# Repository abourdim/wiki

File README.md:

# Wiki

Personal notes and how-to guides.

Every article is available in French (default), English, and Arabic (RTL). The bare filename is the French version; add `-en` or `-ar` for the other languages (e.g. `bit-rxy.html` = French, `bit-rxy-en.html` = English, `bit-rxy-ar.html` = Arabic). Each page has a language switcher in its masthead.

## Contents

- Sharing Files Between Ubuntu & Windows 11 — Step-by-step guide to setting up SMB file sharing in both directions on a local network, plus RDP and troubleshooting notes. [FR](windows-ubuntu-file-sharing-tutorial.html) · [EN](windows-ubuntu-file-sharing-tutorial-en.html) · [AR](windows-ubuntu-file-sharing-tutorial-ar.html)
- VideoCar — Enhanced firmware and web control page for the keyestudio ESP32-CAM Video Smart Car: joystick control, failsafe, live Vision overlays, autonomous Follow-me/Line/Colour-chase modes. [FR](video-car.html) · [EN](video-car-en.html) · [AR](video-car-ar.html)
- Bit-Bot — AI robot companion for kids: voice chat with a choice of AI providers, 12 personalities, AI-powered mini-games, and an optional BBC micro:bit link over Bluetooth. [FR](bit-bot.html) · [EN](bit-bot-en.html) · [AR](bit-bot-ar.html)
- Talking Robot — Browser speech & emotion robot: text-to-speech, speech recognition, 13 animated emotions, and an optional BBC micro:bit link over Bluetooth. No AI provider, fully offline. [FR](talking-robot.html) · [EN](talking-robot-en.html) · [AR](talking-robot-ar.html)
- micro:bit Playground — 8-tab BLE control panel and sensor dashboard for the BBC micro:bit V2: live sensor graphing, servo control, 5 interactive 3D robot models, and a 30+ command firmware protocol. [FR](bit-playground.html) · [EN](bit-playground-en.html) · [AR](bit-playground-ar.html)
- Micro:bit Remote Builder (bit-rxy) — Drag-and-drop BLE remote-control builder: design a layout from 12 widget types and it generates matching MakeCode firmware automatically, with one-click flashing over Bluetooth Partial Flashing Service or WebUSB. [FR](bit-rxy.html) · [EN](bit-rxy-en.html) · [AR](bit-rxy-ar.html)
- ESP32-RXY — ESP32 firmware that impersonates a BBC micro:bit's BLE UART protocol, so the unmodified rxy web app can connect to a plain ESP32-C3 and drive widgets exactly as it would a real micro:bit. [FR](esp32-rxy.html) · [EN](esp32-rxy-en.html) · [AR](esp32-rxy-ar.html)
- rxy-web — The universal Bluetooth remote for rxy robots: the robot owns the layout, so the app knows no robot in advance — it asks whichever one it just found to send its own interface, then draws it. 20 widget types, a layout-fingerprint cache, and a radar fed by two values the robot already sends. [FR](rxy-web.html) · [EN](rxy-web-en.html) · [AR](rxy-web-ar.html)
- Servo-Sonar — A reduced bit-rxy: two continuous-rotation drive servos, one HC-SR04, and nothing else. Four firmware-served panels, and per-wheel trim sliders that are set from the app while driving and kept in NVS. [FR](servo-sonar.html) · [EN](servo-sonar-en.html) · [AR](servo-sonar-ar.html)
- ESP32-CAM Robot -- Wi-Fi rover on a single ESP32-CAM: live MJPEG video, two motors on a TB6612FNG, record-and-replay programs kept on the robot, and a web interface the firmware serves itself. Includes the LEDC timer collision that let the camera clock silently saturate the left motor's PWM. [FR](cam-robot.html) · [EN](cam-robot-en.html) · [AR](cam-robot-ar.html)
- ESP32-CAM Robot m1 -- The same ESP32-CAM with a different motor board: one low-side MOSFET per motor, so no reverse at all. What it has instead is colour following computed in the browser, an engine sound whose pitch tracks the motor PWM, and a captive portal that opens the robot page without anyone typing an address. [FR](cam-robot-m1.html) · [EN](cam-robot-m1-en.html) · [AR](cam-robot-m1-ar.html)
- ESP32-CAM plugin board — ESPHome validation -- An ESPHome test firmware that checks every part of a freshly assembled ESP32-CAM plugin board from a web page: OLED, RGB LED, two L9110 motors, camera and power supply. Pinout taken from the schematic, live camera settings, and the ESPHome traps met during bring-up. Configuration: [files/esp32_cam_test.yaml](files/esp32_cam_test.yaml). KiCad project: [files/esp32_cam_plugin/](files/esp32_cam_plugin/). [FR](cam-plugin-esphome.html) · [EN](cam-plugin-esphome-en.html) · [AR](cam-plugin-esphome-ar.html)
- ESP32-CAM Robot v2 — ESPHome firmware -- Robot firmware for the ESP32-CAM + plugin board v3 (L9110s not fitted) + robot board v2 stack: TB6612 differential drive from a web page or REST, speed ramp, brake, command timeout and stop on link loss, four status RGB LEDs, OLED pages and MJPEG video. Ships with launch.sh, a coloured menu for kids that shows every command it runs. Configuration: [files/esp32_cam_robot.yaml](files/esp32_cam_robot.yaml). Helper: [files/launch.sh](files/launch.sh). KiCad and production files: [files/esp32_cam_robot_v2/](files/esp32_cam_robot_v2/) and [files/esp32_cam_plugin_v3/](files/esp32_cam_plugin_v3/). [FR](cam-robot-esphome.html) · [EN](cam-robot-esphome-en.html) · [AR](cam-robot-esphome-ar.html)

## Index

Open [index.html](index.html) (French), [index-en.html](index-en.html), or [index-ar.html](index-ar.html) for a browsable landing page of all guides.

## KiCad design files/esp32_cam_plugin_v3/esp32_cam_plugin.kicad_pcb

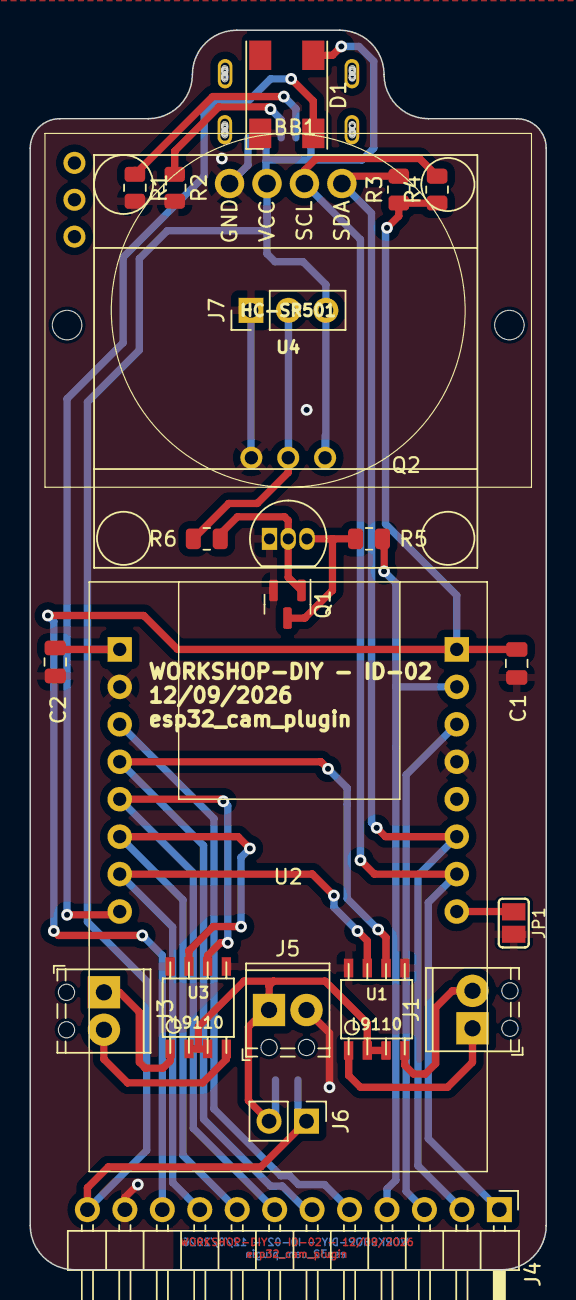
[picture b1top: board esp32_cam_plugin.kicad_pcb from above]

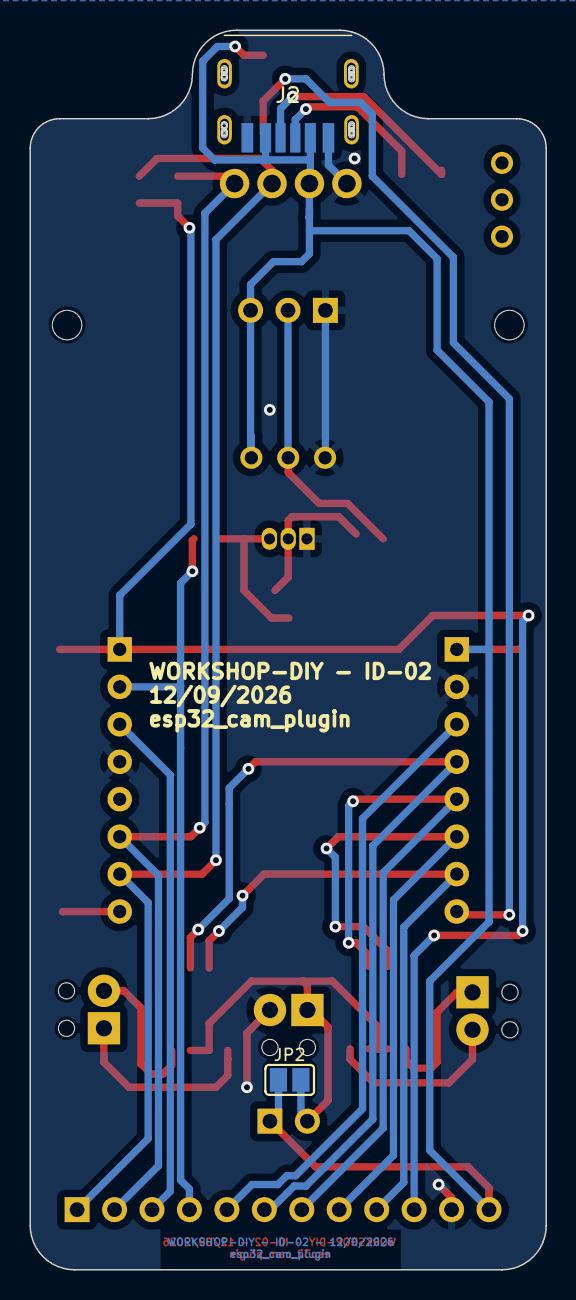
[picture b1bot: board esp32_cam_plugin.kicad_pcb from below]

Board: 2 copper layers, 35.0 x 84.1 mm, 25 parts (2 on the bottom side), 24 nets.

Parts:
BB1: oled_128x32; oled_128X64_no_holes
C1, C2: 100nF; C_0805_2012Metric
D1: led_tx1812db_5050; led_tx1812cxa_5050_hand_soldering
J1, J3, J5: Screw_Terminal_01x02; TerminalBlock_Phoenix_MPT-0,5-2-2.54_1x02_P2.54mm_Horizontal
J2: USB_C_Receptacle_PowerOnly_6P; TYPEC31M17
J4: Conn_01x12_Pin; PinHeader_1x12_P2.54mm_Horizontal
J6: Conn_01x02_Pin; PinHeader_1x02_P2.54mm_Vertical
J7: Conn_01x03_Pin; PinHeader_1x03_P2.54mm_Vertical
JP1, JP2: SolderJumper_2_Open; SJ_OPEN
Q1: MMBT3904; SOT-23
Q2: 2N3904; TO-92_Inline
R1, R2: 5.1K; R_0805_2012Metric
R3, R4: 10K; R_0805_2012Metric
R5: 10k; R_0805_2012Metric
R6: 1k; R_0805_2012Metric
U1, U3: L9110; so-8
U2: ESP32-CAM
U4: HC-SR501

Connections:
3V3: C1.1, J4.10, R3.1, R4.1, U2.9 (3V3)
+5V: BB1.2 (VCC), C2.1, D1.1 (VDD), J2.A9 (VBUS), J2.B9 (VBUS), J4.12, J6.1, J7.3, JP2.1 (A), U2.8 (5V), U4.6 (VCC)
GND: BB1.1 (GND), C1.2, C2.2, D1.3 (GND), J2.A12 (GND), J2.B12 (GND), J4.11, J5.2, J7.1, JP1.2 (B), Q1.2 (E), Q2.1 (E), R1.2, R2.2, U1.5 (GND), U1.8 (GND), U2.7 (GND_1), U2.12 (GND_2), U3.5 (GND), U3.8 (GND), U4.4 (GND)
unnamed: J1.1, U1.1 (OA)
unnamed: J1.2, U1.4 (OB)
unnamed: J2.A5 (CC1), R2.1
unnamed: J2.B5 (CC2), R1.1
unnamed: J3.1, U3.1 (OA)
unnamed: J3.2, U3.4 (OB)
unnamed: J7.2, R6.1, U4.5 (VOUT)
unnamed: JP1.1 (A), U2.16 (GND_3)
unnamed: Q1.1 (B), Q2.2 (B), R6.2
unnamed: Q1.3 (C), Q2.3 (C), R5.1
VCC: J5.1, J6.2, JP2.2 (B), U1.2 (VCC), U1.3 (VCC), U3.2 (VCC), U3.3 (VCC)
esp32_io_00: J4.3, U2.11 (IO0)
esp32_io_02: J4.9, U1.7 (IB), U2.2 (IO2)
esp32_io_04: D1.4 (DIN), U2.1 (IO4)
esp32_io_12: J4.5, U2.6 (IO12)
esp32_io_13: J4.6, U1.6 (IA), U2.5 (IO13)
esp32_io_14: J4.8, U2.3 (IO14), U3.7 (IB)
esp32_io_15: J4.7, U2.4 (IO15), U3.6 (IA)
esp32_io_16: J4.4, R5.2, U2.10 (IO16)
ftdi_rx: BB1.3 (SCL), J4.1, R4.2, U2.15 (U0T)
ftdi_tx: BB1.4 (SDA), J4.2, R3.2, U2.14 (U0R)

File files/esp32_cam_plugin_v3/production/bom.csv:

Designator,Footprint,Quantity,Value,LCSC Part #
BB1,oled_128X64_no_holes,1,oled_128x32,
"C1, C2",0805,2,100nF,
D1,led_tx1812cxa_5050_hand_soldering,1,led_tx1812db_5050,
"J1, J3, J5","TerminalBlock_Phoenix_MPT-0,5-2-2.54_1x02_P2.54mm_Horizontal",3,Screw_Terminal_01x02,
J2,TYPEC31M17,1,USB_C_Receptacle_PowerOnly_6P,
J4,PinHeader_1x12_P2.54mm_Horizontal,1,Conn_01x12_Pin,
J6,PinHeader_1x02_P2.54mm_Vertical,1,Conn_01x02_Pin,
J7,PinHeader_1x03_P2.54mm_Vertical,1,Conn_01x03_Pin,
"JP1, JP2",SJ_OPEN,2,SolderJumper_2_Open,
Q1,SOT-23,1,MMBT3904,
Q2,TO-92_Inline,1,2N3904,
"R1, R2",0805,2,5.1K,
"R3, R4, R5",0805,3,10K,
R6,0805,1,1k,
"U1, U3",so-8,2,L9110,
U2,ESP32-CAM,1,ESP32-CAM,
U4,HC-SR501,1,HC-SR501,

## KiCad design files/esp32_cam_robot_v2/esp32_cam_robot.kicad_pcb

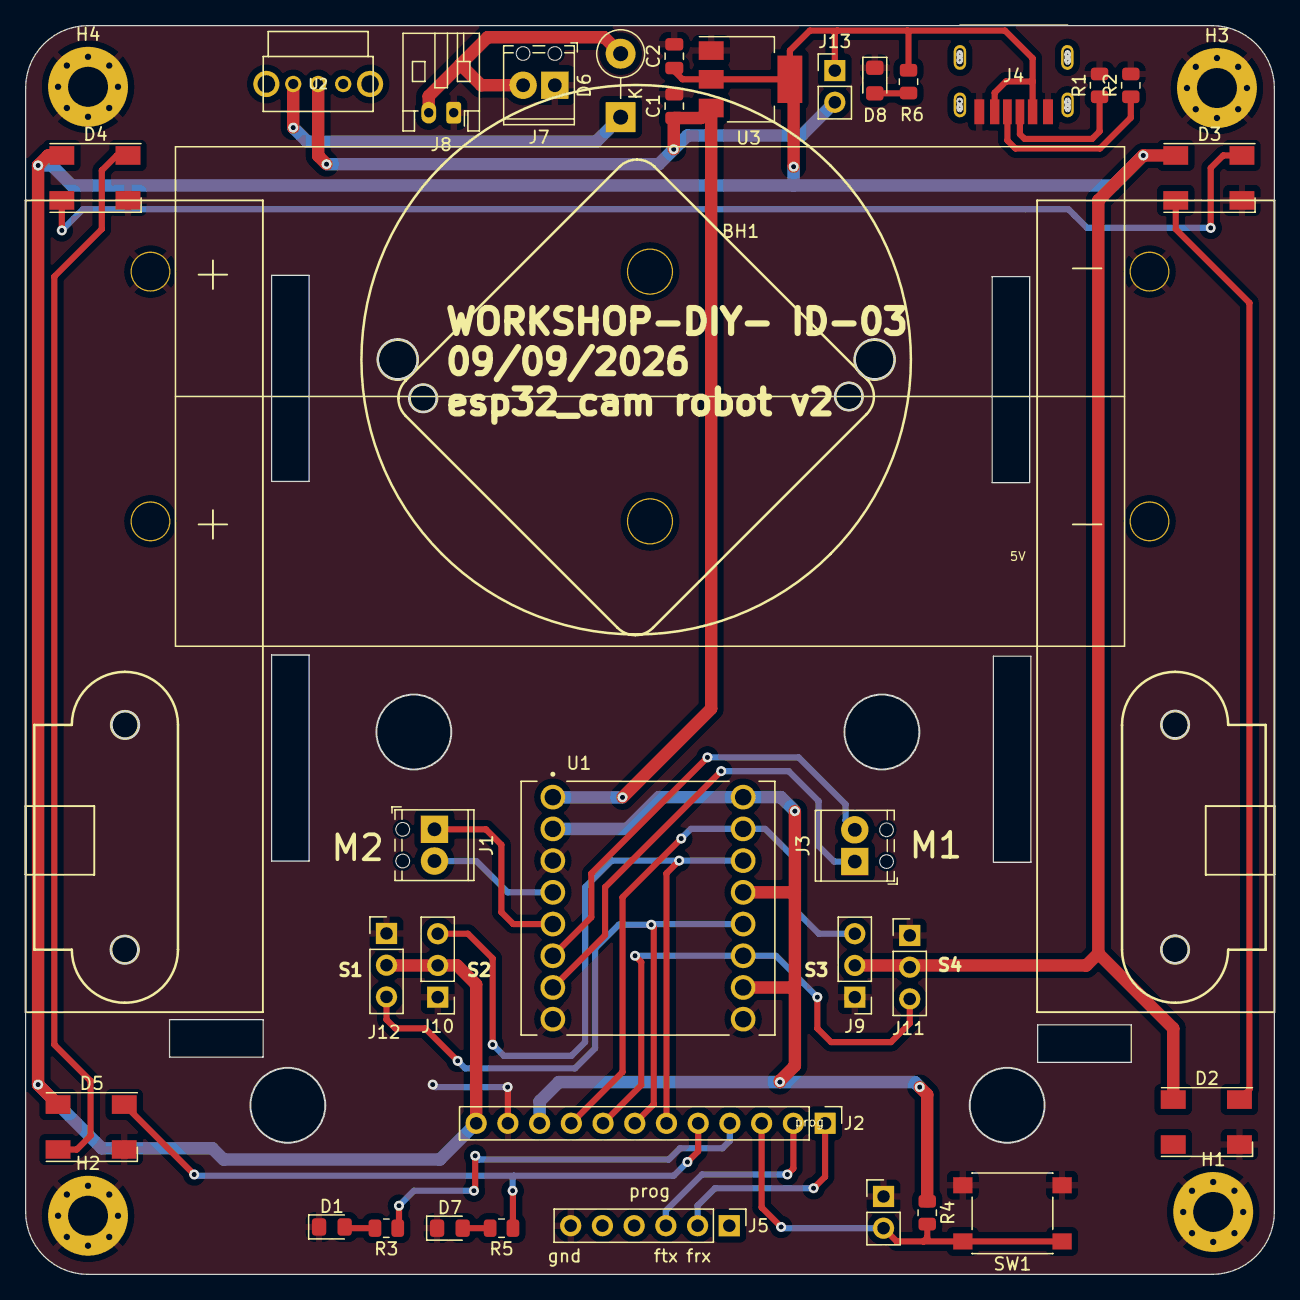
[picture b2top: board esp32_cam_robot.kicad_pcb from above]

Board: 2 copper layers, 100.0 x 100.0 mm, 38 parts (0 on the bottom side), 27 nets.

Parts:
BH1: HOLDER_18650; holder_18650_2
C1, C2: C; C_0805_2012Metric
D1, D7, D8: LED; LED_0805_2012Metric_Pad1.15x1.40mm_HandSolder
D2, D3, D4, D5: led_tx1812db_3528; led_tx1812cxa_5050_hand_soldering
D6: 1N4007; D_DO-15_P5.08mm_Vertical_KathodeUp
H1, H2, H3, H4: MountingHole_Pad; MountingHole_3.2mm_M3_Pad_Via
J1, J3, J7: Screw_Terminal_01x02; TerminalBlock_Phoenix_MPT-0,5-2-2.54_1x02_P2.54mm_Horizontal
J2: Conn_01x12_Pin; PinHeader_1x12_P2.54mm_Vertical
J4: USB_C_Receptacle_PowerOnly_6P; TYPEC31M17
J5: Conn_01x06_Pin; PinHeader_1x06_P2.54mm_Vertical
J6, J13: Conn_01x02_Pin; PinHeader_1x02_P2.54mm_Vertical
J8: Conn_01x02_Pin; JST_PH_S2B-PH-K_1x02_P2.00mm_Horizontal
J9, J10, J11, J12: Conn_01x03_Pin; PinHeader_1x03_P2.54mm_Vertical
R1, R2: 5.1K; R_0805_2012Metric
R3, R5, R6: R; R_0805_2012Metric
R4: 10k; R_0805_2012Metric
SW1: SW_Omron_B3FS; SW_Push_1P1T_NO_6x6mm_H9.5mm
U1: ROB-14450; MODULE_ROB-14450
U2: SK12D07VG4
U3: AMS1117-5.0; SOT-223-3_TabPin2

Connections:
3V3: J2.10, R4.1, U1.2 (VCC), U1.10 (PWMB), U1.13 (STBY), U1.16 (PWMA)
+5V: C2.1, D2.1 (VDD), D3.1 (VDD), D4.1 (VDD), D5.1 (VDD), J2.12, J4.A9 (VBUS), J4.B9 (VBUS), J9.2, J10.2, J11.2, J12.2, J13.1, R6.1, U3.2 (VO)
GND: BH1.1 (+), BH1.2 (-), C1.2, C2.2, D1.1 (K), D2.3 (GND), D3.3 (GND), D4.3 (GND), D5.3 (GND), D7.1 (K), D8.1 (K), H1.1, H2.1, H3.1, H4.1, J2.11, J4.A12 (GND), J4.B12 (GND), J5.6, J6.1, J7.1, J8.1, J9.1, J10.1, J11.1, J12.1, R1.2, R2.2, SW1.2, U1.3 (GND), U1.8 (GND), U1.9 (GND), U3.1 (GND)
unnamed: D1.2 (A), R3.2
unnamed: D2.4 (DIN), D3.2 (DOUT)
unnamed: D3.4 (DIN), D4.2 (DOUT)
unnamed: D4.4 (DIN), D5.2 (DOUT)
unnamed: D6.1 (K), U2.2
unnamed: D7.2 (A), R5.2
unnamed: D8.2 (A), R6.2
unnamed: J1.1, U1.5 (A02)
unnamed: J1.2, U1.4 (A01)
unnamed: J3.1, U1.7 (B01)
unnamed: J3.2, U1.6 (B02)
unnamed: J4.A5 (CC1), R1.1
unnamed: J4.B5 (CC2), R2.1
VCC: C1.1, J13.2, U1.1 (VM), U2.COM, U3.3 (VI)
VDDA: D6.2 (A), J7.2, J8.2
esp32_io_00: J2.3, J6.2, R4.2, SW1.1
esp32_io_02: J2.9, J9.3, U1.15 (AI2)
esp32_io_12: D5.4 (DIN), J2.5, R5.1
esp32_io_13: J2.6, J10.3, U1.14 (AI1)
esp32_io_14: J2.8, J11.3, U1.11 (BI2)
esp32_io_15: J2.7, J12.3, U1.12 (BI1)
esp32_io_16: J2.4, R3.1
ftdi_rx: J2.1, J5.2
ftdi_tx: J2.2, J5.3

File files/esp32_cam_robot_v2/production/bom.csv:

Designator,Footprint,Quantity,Value,LCSC Part #
BH1,holder_18650_2,1,HOLDER_18650,
"C1, C2",0805,2,C,
"D1, D7, D8",0805,3,LED,
"D2, D3, D4, D5",led_tx1812cxa_5050_hand_soldering,4,led_tx1812db_3528,
D6,D_DO-15_P5.08mm_Vertical_KathodeUp,1,1N4007,
"H1, H2, H3, H4",MountingHole_3.2mm_M3_Pad_Via,4,MountingHole_Pad,
"J1, J3, J7","TerminalBlock_Phoenix_MPT-0,5-2-2.54_1x02_P2.54mm_Horizontal",3,Screw_Terminal_01x02,
"J10, J11, J12, J9",PinHeader_1x03_P2.54mm_Vertical,4,Conn_01x03_Pin,
"J13, J6",PinHeader_1x02_P2.54mm_Vertical,2,Conn_01x02_Pin,
J2,PinHeader_1x12_P2.54mm_Vertical,1,Conn_01x12_Pin,
J4,TYPEC31M17,1,USB_C_Receptacle_PowerOnly_6P,
J5,PinHeader_1x06_P2.54mm_Vertical,1,Conn_01x06_Pin,
J8,JST_PH_S2B-PH-K_1x02_P2.00mm_Horizontal,1,Conn_01x02_Pin,
"R1, R2",0805,2,5.1K,
"R3, R5, R6",0805,3,R,
R4,0805,1,10k,
SW1,SW_Push_1P1T_NO_6x6mm_H9.5mm,1,SW_Omron_B3FS,
U1,MODULE_ROB-14450,1,ROB-14450,
U2,SK12D07VG4,1,SK12D07VG4,
U3,SOT-223-3_TabPin2,1,AMS1117-5.0,
